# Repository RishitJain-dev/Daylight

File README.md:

# **Daylight**
An alarm clock with a TFT 2.25 inch screen and dial to act as not just a alarm clock, but also as a timer, stopwatch and pomodoro focus timer

  ## 1. Designing the schematic - 1 hour
   I used KiCad to design the schematic, loosely following the guide on Blare.

   https://lapse.hackclub.com/timelapse/PNQWRp-xT5TE
   
 ## 2. Designing the PCB - 1 hour  30 minutes
   Placed components, routed traces, filled a ground pour and exported STEP and GERBER for later use

   https://lapse.hackclub.com/timelapse/aowiD0g3GfD9
   
## 3. Designing the CAD - 1 hour 30 minutes
I used Onshape to design the CAD, splitting the casing into 2 pieces, top and bottom, all connected by nuts and bolts, and keycaps for the switches and a knob for the rotary encoder, and a small hole for the USB-C port

# Bill of Materials
2x Cherry MX Switches

2x Keycaps any colour

1x EC11 Rotary Encoder with switch

1x Seeed XIAO RP2040

4x M3 Nut and Bolt, 2cm, Low profile top

4x M3 Spacers, 3mm diameter, 0.6cm, circular, non-threaded

1 Case (2 printed parts)

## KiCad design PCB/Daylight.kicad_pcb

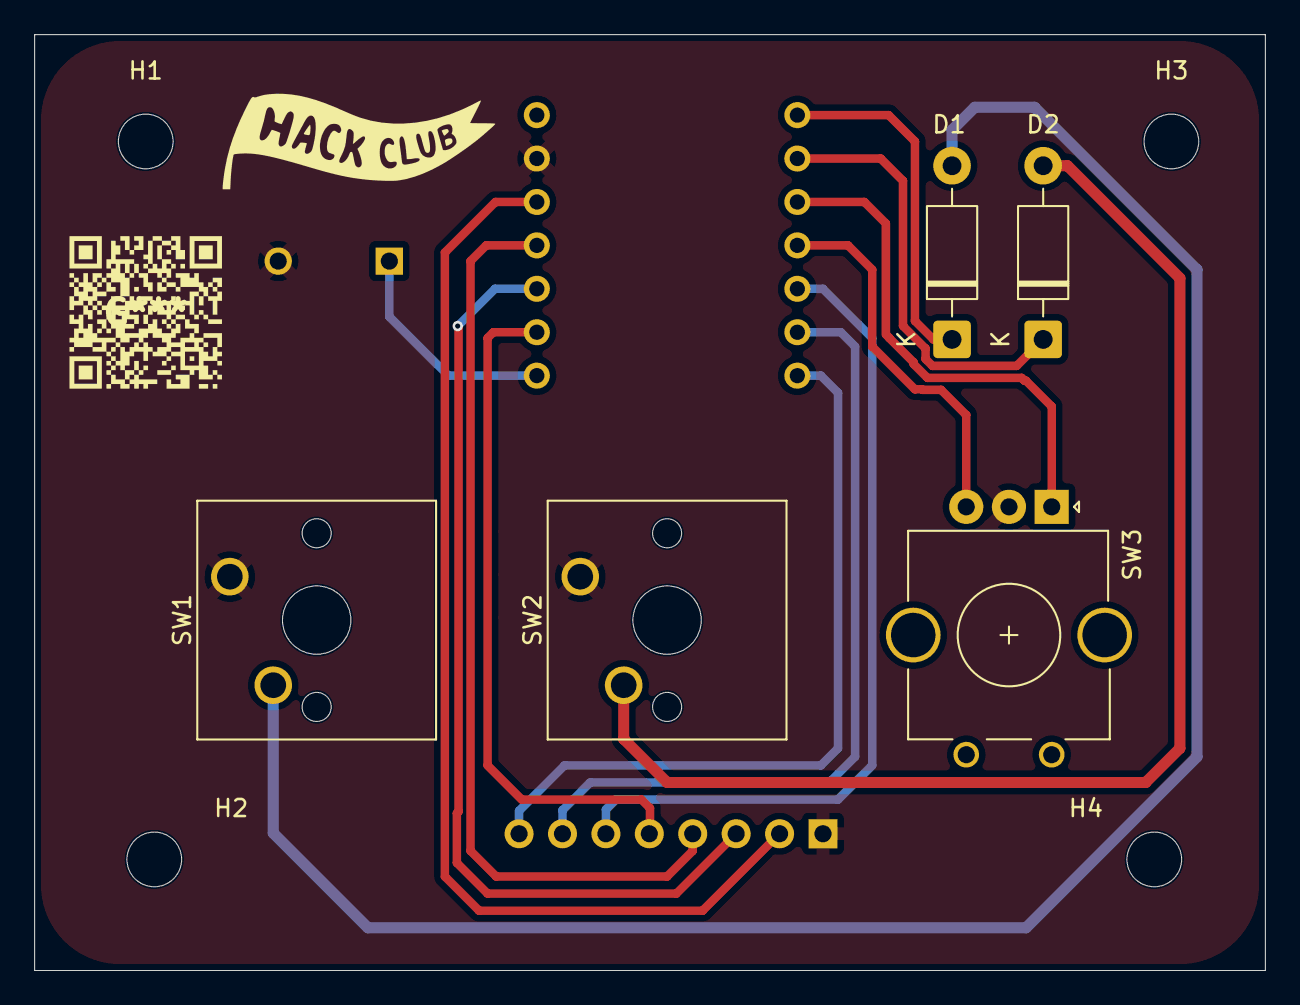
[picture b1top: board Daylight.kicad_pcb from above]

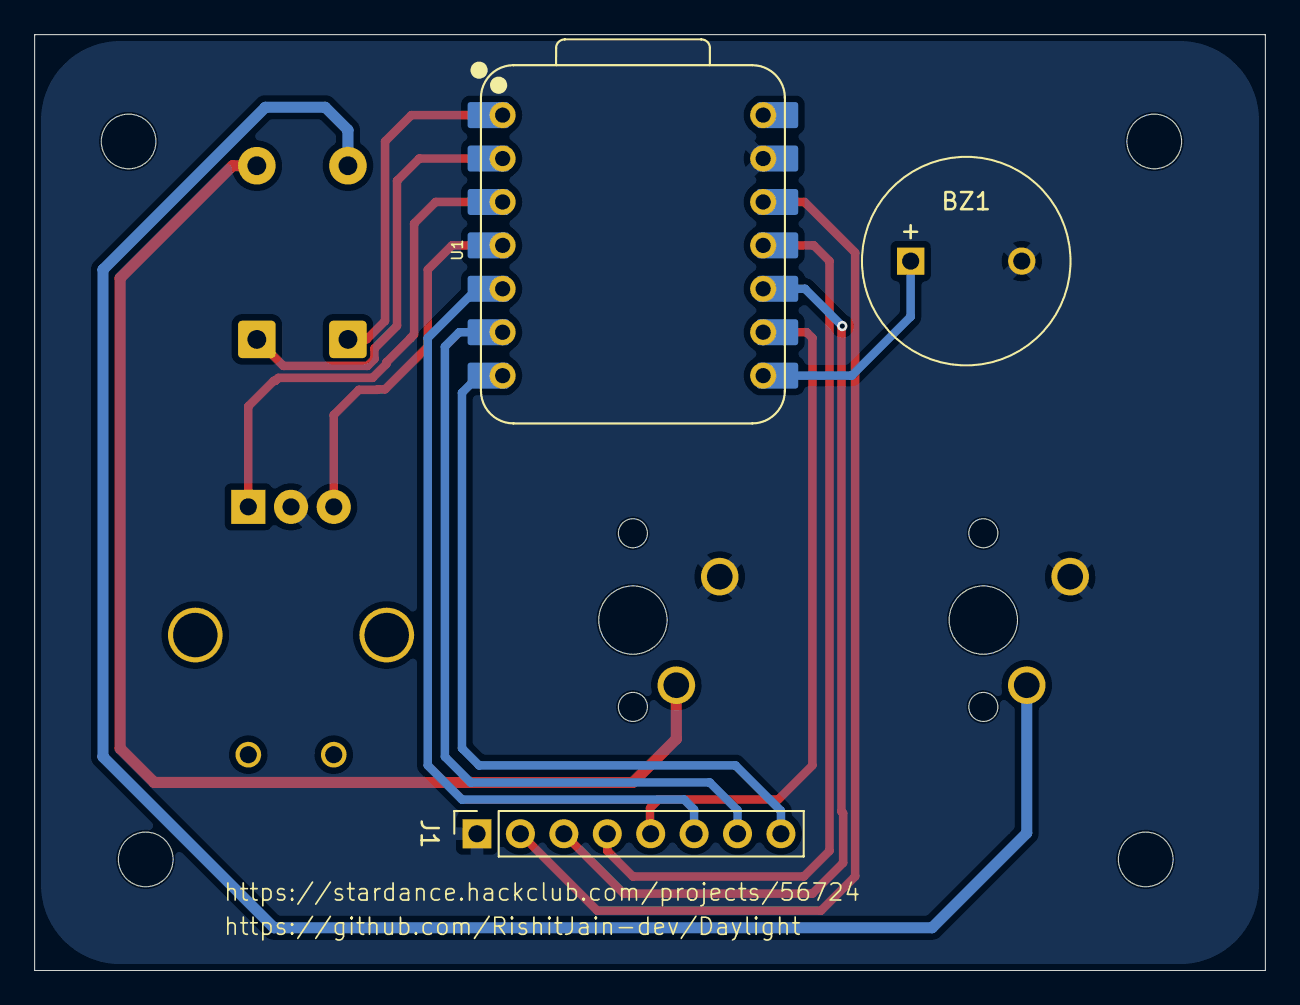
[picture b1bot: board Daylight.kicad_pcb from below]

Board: 2 copper layers, 72.0 x 54.8 mm, 12 parts (3 on the bottom side), 15 nets.

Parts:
BZ1: Buzzer_5V; MagneticBuzzer_ProSignal_ABT-410-RC
D1, D2: 1N4001; D_DO-41_SOD81_P10.16mm_Horizontal
H1, H2, H3, H4: MountingHole; MountingHole_3.2mm_M3
J1: Conn_01x08_Pin; PinSocket_1x08_P2.54mm_Vertical
SW1, SW2: SW_Push; SW_Cherry_MX_1.00u_PCB
SW3: RotaryEncoder; RotaryEncoder_Alps_EC11E_Vertical_H20mm_CircularMountingHol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
U1: XIAO-ESP32-C3-SMD; XIAO-ESP32-C3-DIP

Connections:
+3V3: J1.2, U1.12 (3V3_OUT)
/BL: J1.8, U1.7 (D6)
/CS: J1.7, U1.6 (D5)
/D0: D1.1 (K), U1.1 (D0)
/D1: D2.1 (K), U1.2 (D1)
/D2: SW3.A, U1.3 (D2)
/D3: SW3.B, U1.4 (D3)
/D7: BZ1.1, U1.8 (D7)
/DC: J1.6, U1.5 (D4)
/RST: J1.5, U1.9 (D8)
/SCL: J1.3, U1.10 (D9/BOOT)
/SDA: J1.4, U1.11 (D10)
GND: BZ1.2, J1.1, SW1.1, SW2.1, SW3.C, U1.13 (GND)
unnamed: D1.2 (A), SW1.2
unnamed: D2.2 (A), SW2.2
